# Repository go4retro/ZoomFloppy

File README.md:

# ZoomFloppy

## Introduction

ZoomFloppy brings Commodore disk archival into the 21st  Century, bridging the gap between the both the IEEE-488 and IEC-based  disk intelligent Commodore™ disk drive line and contemporary personal  computers. Taking up the baton from the ever-popular X\*-1541 line of  parallel port interfaces, ZoomFloppy provides complete functionality for newer machines running multitasking and multi-user operating systems  and those systems lacking the legacy parallel port upon which the  X\*-1541 interfaces depend.

Designed by Commodore enthusiast Nate Lawson, ZoomFloppy utilizes the ubiquitous [OpenCBM](http://sourceforge.net/projects/opencbm/) Commodore device access libraries and application utilities for  operation. In addition, applications like the VICE Emulator that include OpenCBM support will work with ZoomFloppy as well. Use ZoomFloppy and  VICE to access actual Commodore IEC-based serial devices like the  VIC-1541 disk drive or IEEE-488 based devices like the CBM 8050 from  your emulator!

ZoomFloppy works in conjunction with the feature-rich OpenCBM media archiving suite maintained and supported by a team led by Spiro Trikaliotis. The open source OpenCBM  software supports Unix/Linux/*BSD systems, Macintosh OS X machines, as well as  Microsoft Windows XP, Windows Vista, Windows 7, and Windows 10.  Spiro Trikaliotis has provided a convenient installation [manual](http://opencbm.trikaliotis.net/opencbm-8.html) for multi-platform installation. 

ZoomFloppy offers unparalleled performance and robustness for the  serious Commodore enthusiast. Archive data while playing games, writing letters, or listening to videos without any loss of data fidelity.  Designed for the sometimes demanding nature of today’s applications,  ZoomFloppy handles such requirements with ease. ZoomFloppy will find a  cherished home in your Commodore computer setup.

Here’s a talk I gave on ZoomFloppy at the 2011 World of Commodore Expo: https://www.youtube.com/watch?v=RNcVtMDFbOg

## Specifications

ZoomFloppy comprises a circuit board containing an Atmel ATMEGA32U2  microcontroller and support circuitry. The ZoomFloppy interface  includes on board ports for IEC-based disk drives, connectors for the  various Commodore drive parallel cabling systems, and IEEE-488  connectors for future expansion capabilities. The entire unit can be  installed in a standard Hammond plastic enclosure for a truly  professional look. A mini-USB port provides power and PC connectivity.

The [ZoomFloppy Schematic and PCB](https://github.com/go4retro/ZoomFloppy) are released under a Creative Commons Share Alike v4.0 license in both EAGLE CAD and high resolution PNG file formats.

## Requirements

- PC/Mac with available USB 2.0 port
- USB to mini-USB cable (not supplied)
- IEC disk drive cable (available separately).

## Support

Users can ask questions and discuss their units on the [ZoomFloppy Users](http://groups.google.com/group/zoomfloppy-users) web forum/mailing list, while obtaining more information on software usage via the [OpenCBM](https://sourceforge.net/p/opencbm/mailman/opencbm-user/) mailing list.

Units come with a 30 days return policy and 1 year warranty.

## Purchase

ZoomFloppy can be purchased at the [RETRO Innovations online store](http://store.go4retro.com/products/ZoomFloppy.html).

## Frequently Asked Questions

### How is the Zoom Floppy different then the XU1541?

- Performance

  - 25-second backup without optimizing (parallel transfer, needs cable in drive).
  - Still faster even for serial xfers.
- Functionality

  - supports Burst Nibbler protocol via nibtools. Allows raw g64 backups (read and write). Works with vmax/epyx etc etc.
- Reliability

  -  interrupt xfers in the middle (^C), start another transfer, and everything gets reset and restarted properly
  -  Supports infinite holdoff 
- Cost

  - currently $35 USD
- IEEE-488 Support

  -  ZoomFloppy is one of a few solutions for USB access to the IEE-488 drives, and the only one that understands PET/CBM IEEE commands.
- Future Expansion

  - All signals are available on the X5 Expansion Port.
  -  only 7 KB used out of 32 KB FLASH on microcontroller

### Can I use the ZoomFloppy to copy D64 images to real disks?

Yes, simply install the OpenCBM software and then use d64copy to transfer D64 images to a real 1541.

### Will ZoomFloppy allow parallel cables to operate?

Yes, ZoomFloppy provides both DB15-M, a 2×8 header, and a 12/24 .156″ connector for various parallel cable options. XAP1541-compatible  cables will plug into the DB15 connector, while old user port cables can connect to the 12/24 edge connector on the board.

### Does RETRO Innovations sell parallel cable kits?

Not yet. RETRO Innovations is planning a parallel cable kit (DB15-F  connector and 6522 daughterboard for the 1541 and a DB15M-F cable), but  current purchasers can create their own cable via Peter Scheper’s [Parallel Cable](http://ist.uwaterloo.ca/~schepers/cables.html) page.

### How does ZoomFloppy compare to a XUM1541 device?

ZoomFloppy is an implementation of an XUM1541-compliant interface.  XUM1541 specifies a protocol that is used to transfer data from the  interface to the OpenCBM libraries. In many cases, the terms can be  used interchangeably, though they do not mean exactly the same thing.  Incidentally, ZoomFloppy is partially named after the “xum” in XUM1541,  which many people pronounce as “zoom” .

### I received the unit and plugged it in, but it does not work. What do I do?

Are you using a USB hub? If so, try plugging the ZF directly into the PC’s USB port and not into the hub. The hub may be flaky or not have  enough current to support all the devices on USB. If so, one thing that  might help is plugging in an external power source to your hub.

### How do I diagnose a drive issue?

1. Connect just one drive via IEC, no parallel. If that doesn’t work at all, it’s probably the drive. Try a different drive.
2. Add the parallel cable (if any) and retest.
3. Add other drives on IEC bus (up to 4 total) one at a time. Make sure each is powered on and attached via a short serial cable. See if each  is detected after adding.

## Copyright

This project's PCB files are free designs; you can redistribute them 
and/or modify them under the terms of the Creative Commons
Attribution-ShareAlike 4.0 International License.

You should have received a copy of the license along with this
work. If not, see <http://creativecommons.org/licenses/by-sa/4.0/>.

These files are distributed in the hope that they will be useful,
but WITHOUT ANY WARRANTY; without even the implied warranty of
MERCHANTABILITY or FITNESS FOR A PARTICULAR PURPOSE.  See the
license for more details.

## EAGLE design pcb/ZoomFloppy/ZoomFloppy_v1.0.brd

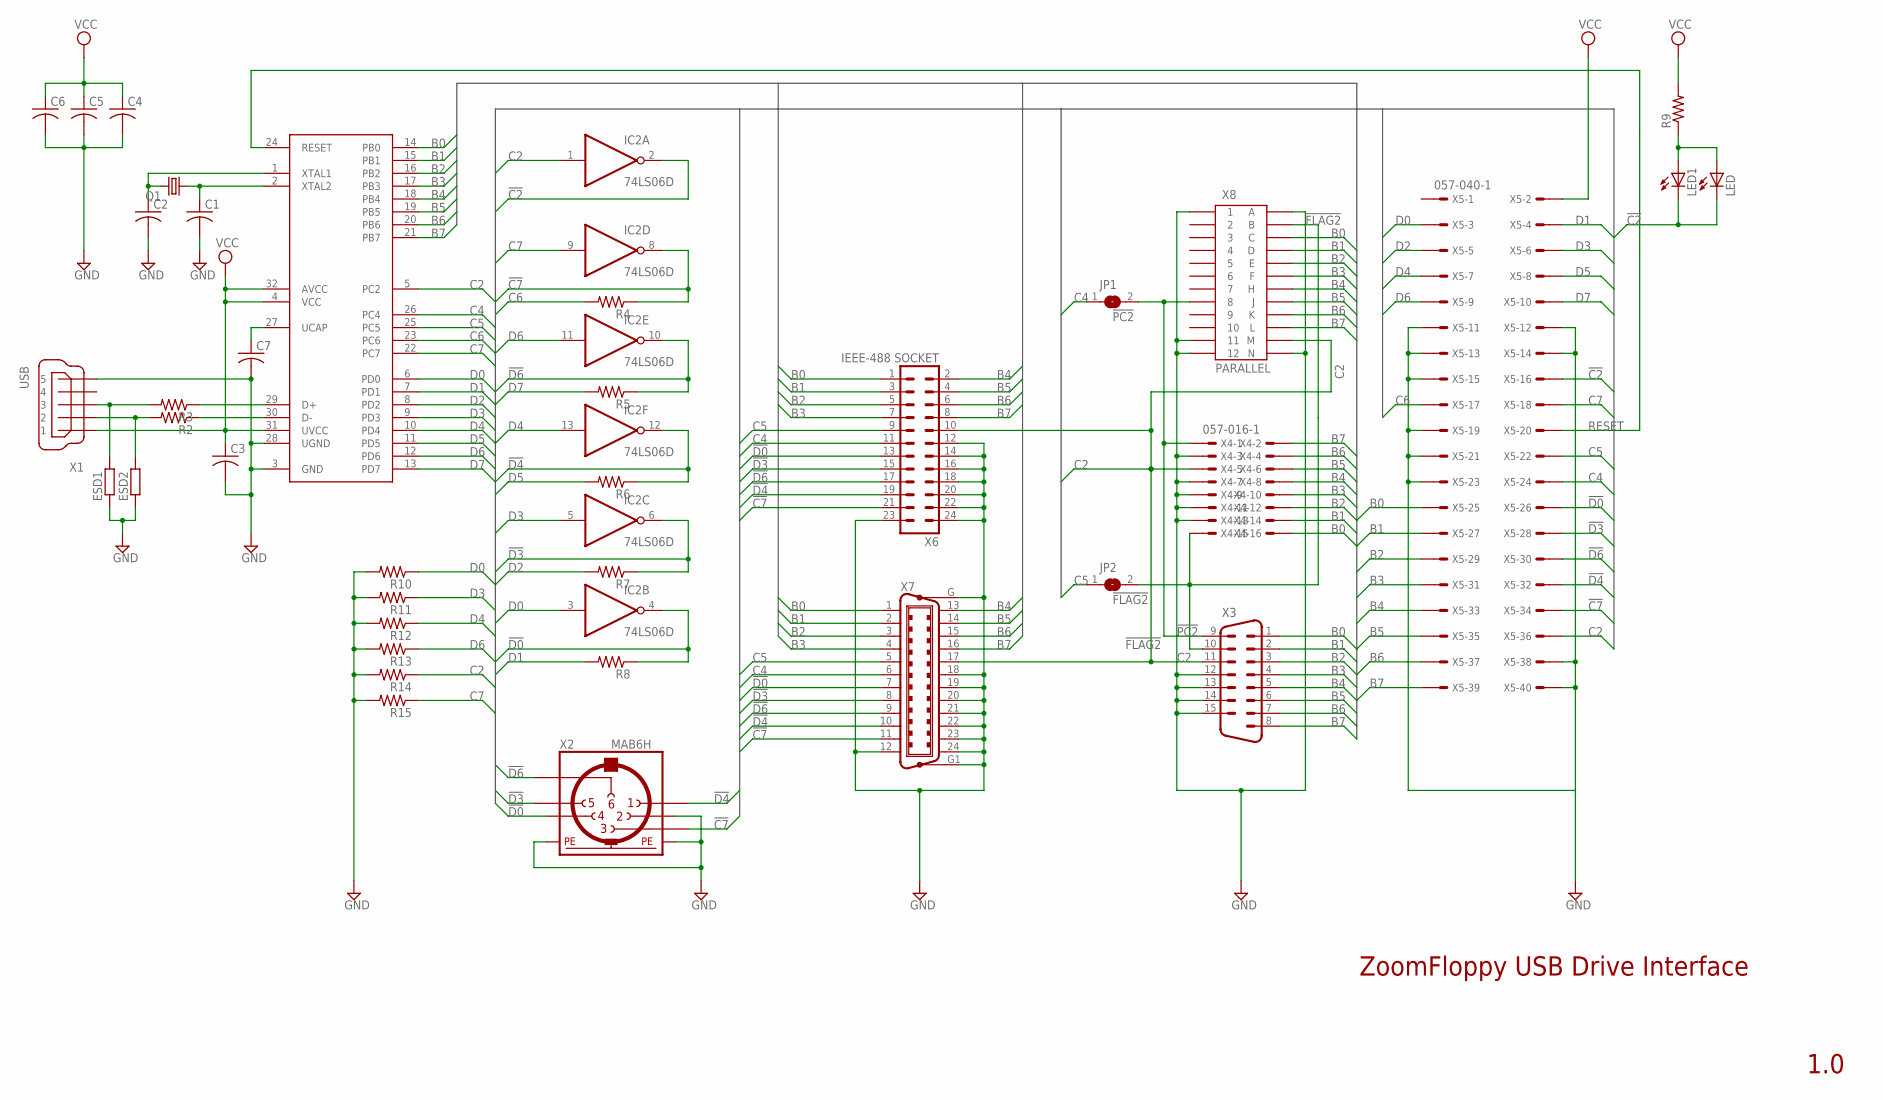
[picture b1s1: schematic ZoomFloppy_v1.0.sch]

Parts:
C1, C2, C3, C4, C5, C6, C7: C-USC0402; C0402
ESD1, ESD2: R-EU_R0603; R0603
IC1: ATMEGA32U2; VQFP32
IC2: 74LS06D; SO14
JP1, JP2: SJ
LED: LED3MM
LED1: LEDCHIP-LED0805; CHIP-LED0805
Q1: CRYSTALHC49UP; HC49UP
R2, R3, R4, R5, R6, R7, R8, R9, R10, R11, R12, R13, R14, R15: R-US_R0402; R0402
X1: USB; UX60-MB-5ST
X2: MAB6H
X3: M15-182; 182-015-MALE
X4: 057-016-1
X5: 057-040-1
X6: IEEE-488 SOCKET; MA12-2
X7: C24HP; 24HP
X8: PARALLEL; MA-24

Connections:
!C2: IC2.2 (O), LED.K (C), LED1.C, X5.16
!C7: IC2.8 (O), R4.1, X2.3, X5.34, X6.21, X7.11
!D0: IC2.4 (O), R8.1, X2.4, X5.26, X6.13, X7.7
!D3: IC2.6 (O), R7.1, X2.5, X5.28, X6.15, X7.8
!D4: IC2.12 (O), R6.1, X2.1, X5.32, X6.19, X7.10
!D6: IC2.10 (O), R5.1, X2.6, X5.30, X6.17, X7.9
!FLAG2: JP2.2, X3.10, X4.15, X8.B
!PC2: JP1.2, X3.9, X4.1, X8.8
B0: IC1.14 (PB0), X3.1, X4.16, X5.25, X6.1, X7.1, X8.C
B1: IC1.15 (PB1), X3.2, X4.14, X5.27, X6.3, X7.2, X8.D
B2: IC1.16 (PB2), X3.3, X4.12, X5.29, X6.5, X7.3, X8.E
B3: IC1.17 (PB3), X3.4, X4.10, X5.31, X6.7, X7.4, X8.F
B4: IC1.18 (PB4), X3.5, X4.8, X5.33, X6.2, X7.13, X8.H
B5: IC1.19 (PB5), X3.6, X4.6, X5.35, X6.4, X7.14, X8.J
B6: IC1.20 (PB6), X3.7, X4.4, X5.37, X6.6, X7.15, X8.K
B7: IC1.21 (PB7), X3.8, X4.2, X5.39, X6.8, X7.16, X8.L
C2: IC1.5 (PC2), IC2.1 (I), R14.1, X3.11, X4.5, X5.36, X6.10, X7.17, X8.M
C4: IC1.26 (PC4), JP1.1, X5.24, X6.11, X7.6
C5: IC1.25 (PC5), JP2.1, X5.22, X6.9, X7.5
C6: IC1.23 (PC6), R4.2, X5.17
C7: IC1.22 (PC7), IC2.9 (I), R15.1, X5.18
D0: IC1.6 (PD0), IC2.3 (I), R10.1, X5.3
D1: IC1.7 (PD1), R8.2, X5.4
D2: IC1.8 (PD2), R7.2, X5.5
D3: IC1.9 (PD3), IC2.5 (I), R11.1, X5.6
D4: IC1.10 (PD4), IC2.13 (I), R12.1, X5.7
D5: IC1.11 (PD5), R6.2, X5.8
D6: IC1.12 (PD6), IC2.11 (I), R13.1, X5.9
D7: IC1.13 (PD7), R5.2, X5.10
GND: C1.2, C2.2, C3.2, C4.2, C5.2, C6.2, C7.2, ESD1.1, ESD2.1, IC1.3 (GND), IC1.28 (UGND), IC2.7 (GND), R10.2, R11.2, R12.2, R13.2, R14.2, R15.2, X1.5, X2.2, X2.PE, X2.PE@ (PE), X3.12, X3.13, X3.14, X3.15, X4.3, X4.7, X4.9, X4.11, X4.13, X5.11, X5.12, X5.13, X5.14, X5.15, X5.19, X5.21, X5.23, X5.38, X5.40, X6.12, X6.14, X6.16, X6.18, X6.20, X6.22, X6.23, X6.24, X7.12, X7.18, X7.19, X7.20, X7.21, X7.22, X7.23, X7.24, X7.G, X7.G1, X8.1, X8.11, X8.12, X8.A, X8.N
unnamed: C2.1, IC1.1 (XTAL1), Q1.2
unnamed: C1.1, IC1.2 (XTAL2), Q1.1
unnamed: LED.A, LED1.A, R9.1
unnamed: ESD1.2, R3.2, X1.3
unnamed: ESD2.2, R2.2, X1.2
unnamed: IC1.29 (D+), R3.1
unnamed: IC1.30 (D-), R2.1
unnamed: C7.1, IC1.27 (UCAP)
RESET: IC1.24 (RESET), X5.20
VCC: C3.1, C4.1, C5.1, C6.1, IC1.4 (VCC), IC1.31 (UVCC), IC1.32 (AVCC), IC2.14 (VCC), R9.2, X1.1, X5.2

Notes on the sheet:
ZoomFloppy USB Drive Interface
1.0

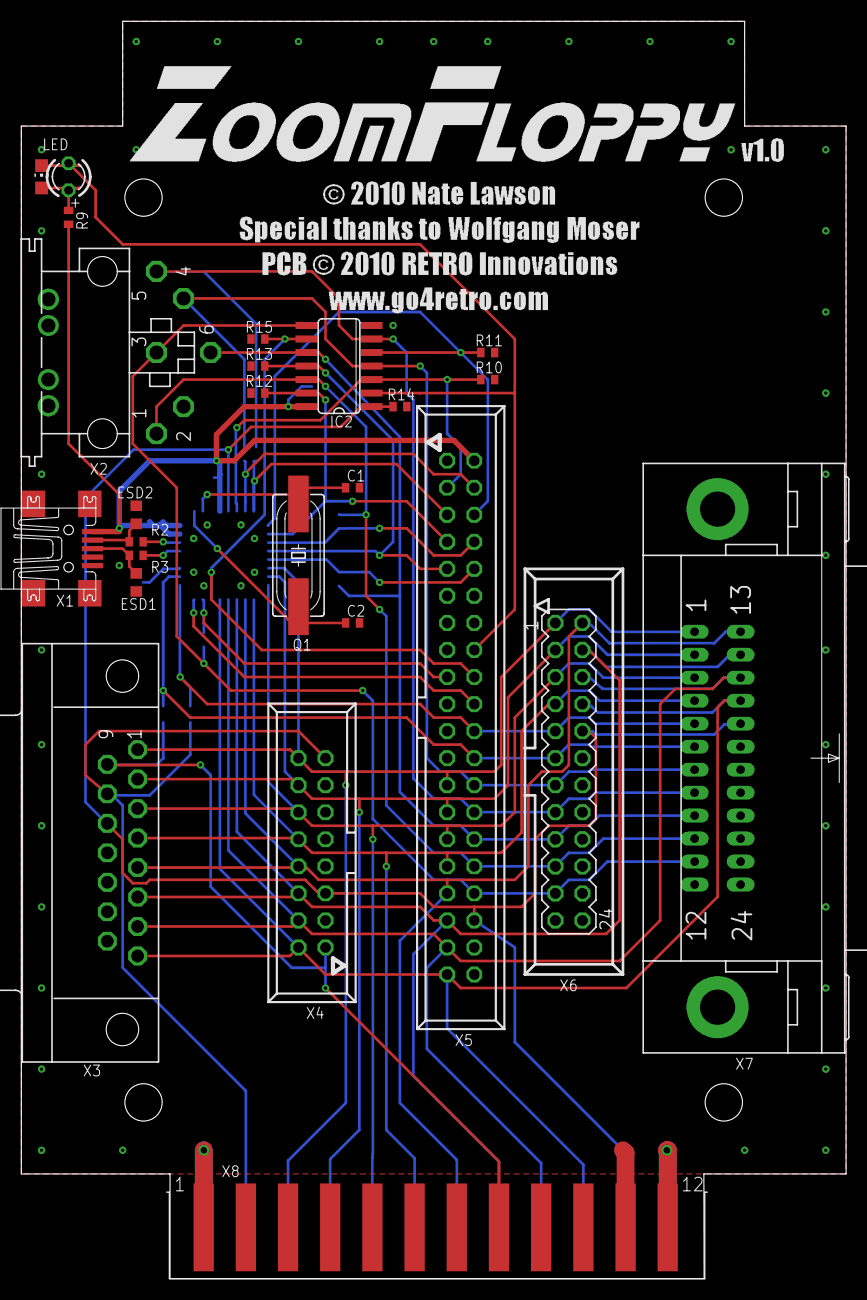
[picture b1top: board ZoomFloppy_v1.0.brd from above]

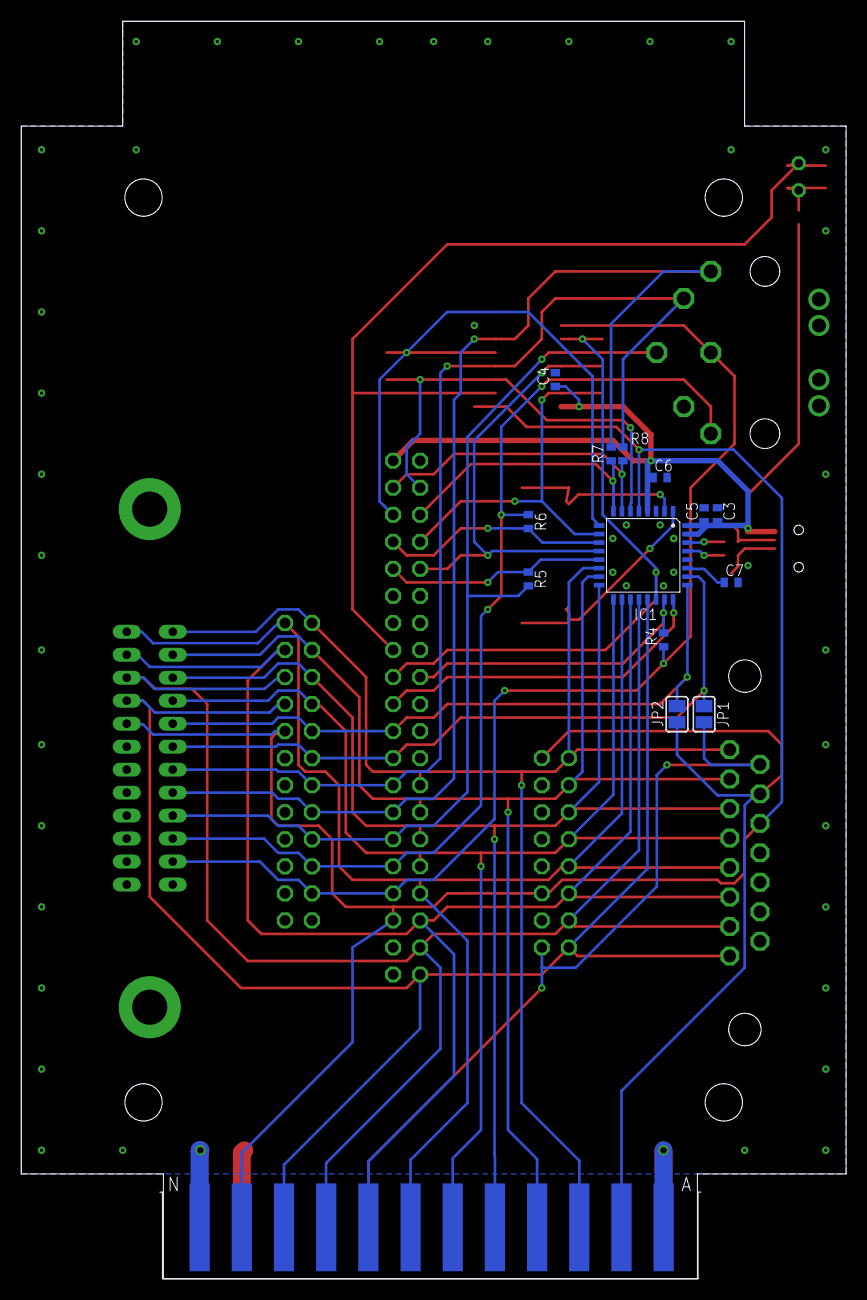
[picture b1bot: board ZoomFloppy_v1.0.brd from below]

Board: 2 copper layers, 77.5 x 118.1 mm, 38 parts (13 on the bottom side), 40 nets.

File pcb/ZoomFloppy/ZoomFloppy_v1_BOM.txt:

ZoomFloppy			
ID	Part Number	Description	Quantity
IC1	atmega32u2-au	ATMEGA 32U2	1
IC2	74ls06	74ls06	1
Q1		16.000MHz 18-20pF	1
"C1,C2"		22pF 0402 SMT	2
C3		10uF 0402 SMT	1
"C4,C5,C6"		.1uF 0402 SMT	3
C7		1.0uF 0402 SMT	1
"R2,R3"		22 0402 SMT	2
R4-R8		4.7K 0402 SMT	5
R9		220 0402 SMT	1
R10-R15		100K 0402 SMT	6
X1	UX60-MB-5ST	Mini USB Type B	1
X2		DIN 6	1
X3		DB15 Male	1
X4		2x16 header	1
"ESD1,ESD2"	PESD0603-240	ESD	1
LED1		LED >150mcd 3mm	1

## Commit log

2020-11-05 Update links in README.md and convert EAGLE files to XML
2020-11-05 Update PNG files
2020-11-05 More updates to README
2020-11-05 Update OpenCBM mailing list URL
